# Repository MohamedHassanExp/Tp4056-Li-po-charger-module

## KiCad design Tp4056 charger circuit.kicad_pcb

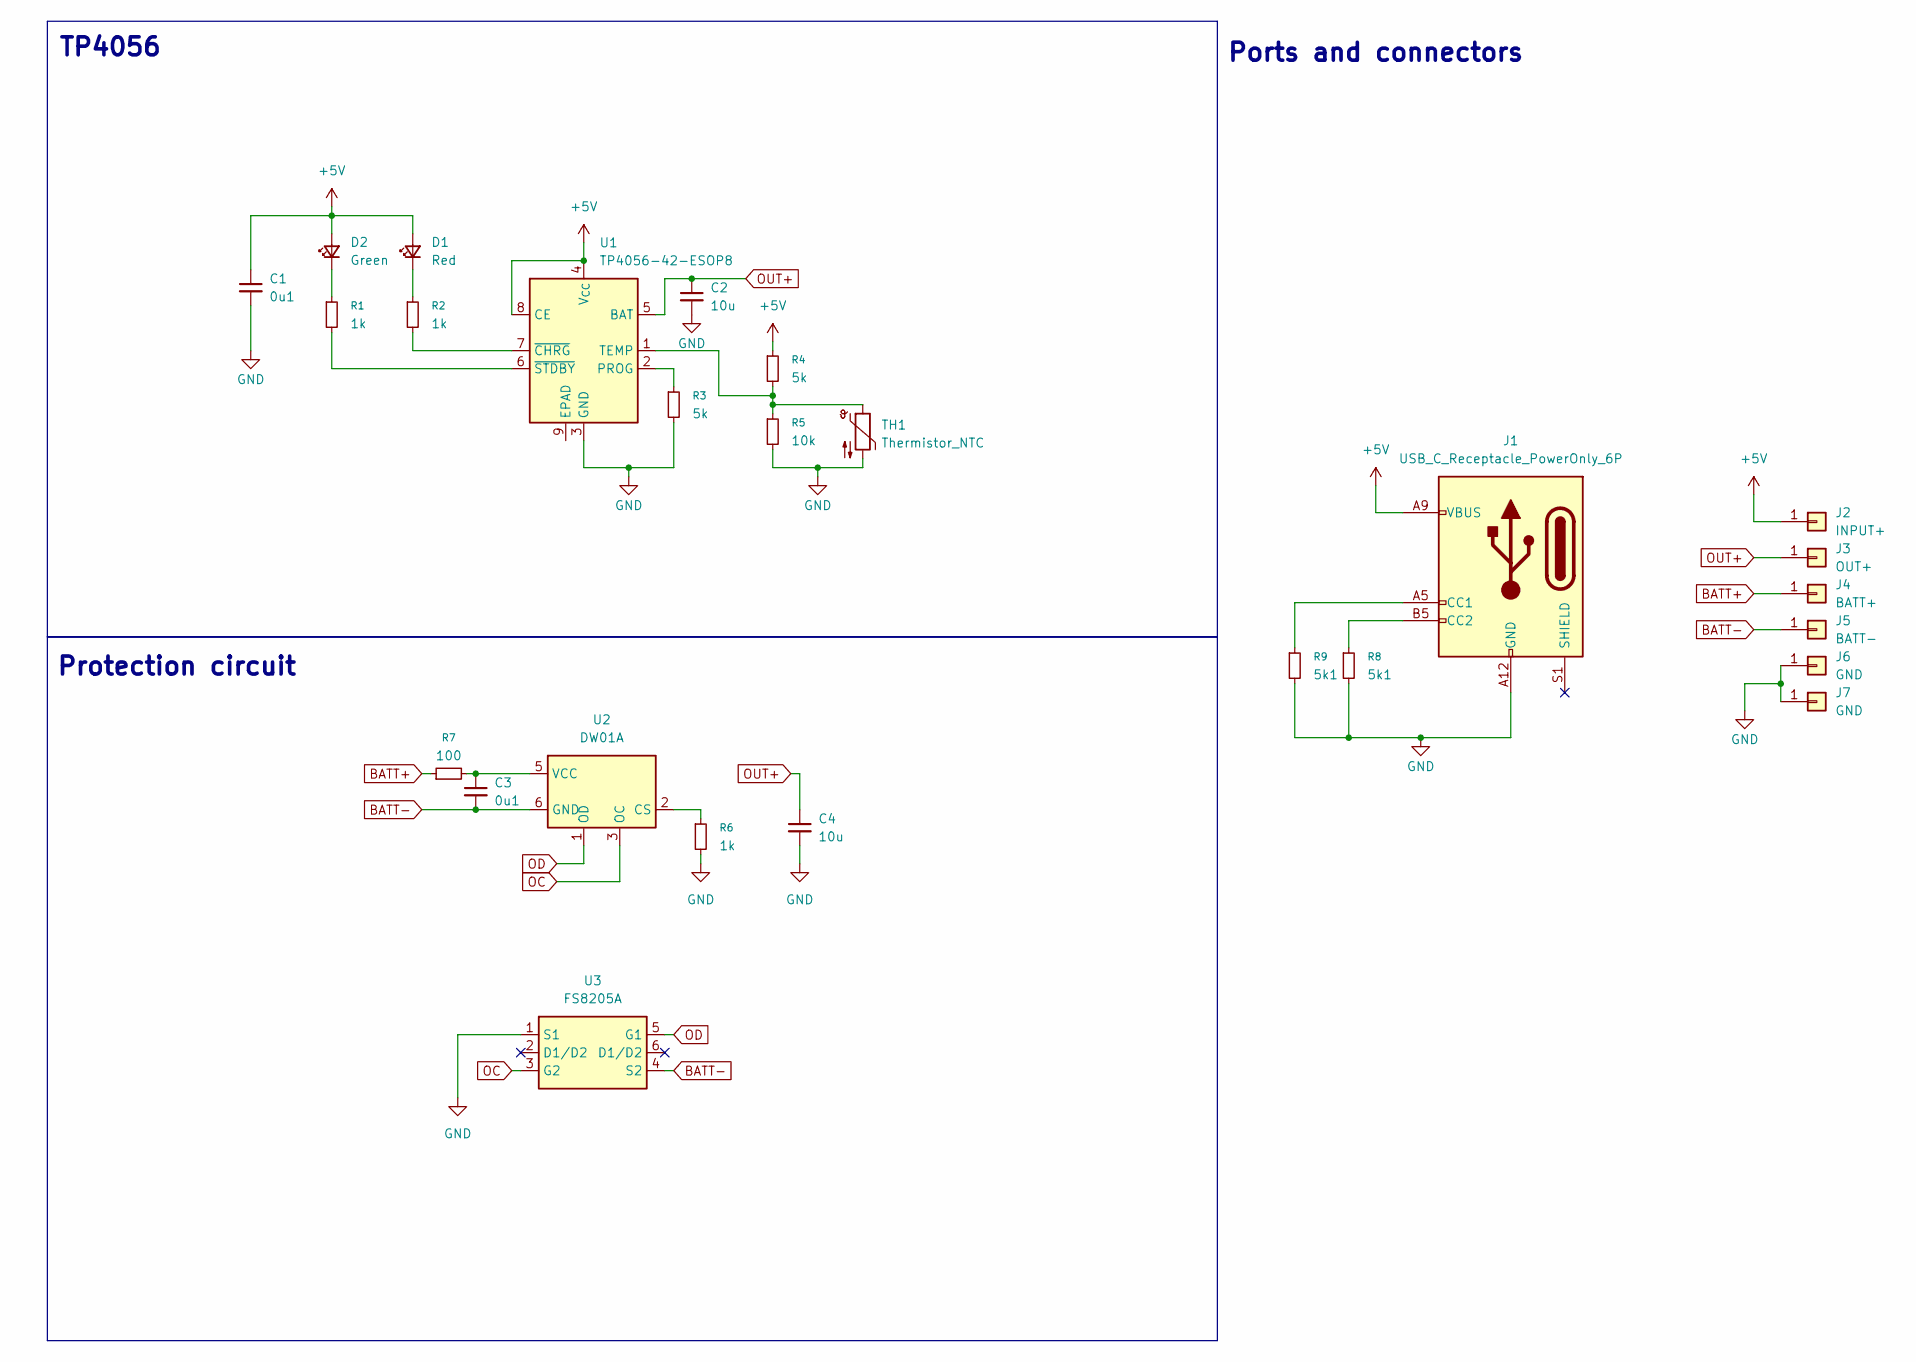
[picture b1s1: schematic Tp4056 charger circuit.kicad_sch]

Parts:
C1, C3: 0u1; C_0603_1608Metric
C2, C4: 10u; C_0603_1608Metric
D1: Red; LED_0603_1608Metric
D2: Green; LED_0603_1608Metric
J1: USB_C_Receptacle_PowerOnly_6P; USB_C_Receptacle_GCT_USB4125-xx-x_6P_TopMnt_Horizontal
J2: INPUT+; TestPoint_THTPad_3.0x3.0mm_Drill1.5mm
J3: OUT+; TestPoint_THTPad_3.0x3.0mm_Drill1.5mm
J4: BATT+; TestPoint_THTPad_3.0x3.0mm_Drill1.5mm
J5: BATT-; TestPoint_THTPad_3.0x3.0mm_Drill1.5mm
J6, J7: GND; TestPoint_THTPad_3.0x3.0mm_Drill1.5mm
R1, R2, R6: 1k; R_0603_1608Metric
R3, R4: 5k; R_0603_1608Metric
R5: 10k; R_0603_1608Metric
R7: 100; R_0603_1608Metric
R8, R9: 5k1; R_0603_1608Metric
TH1: Thermistor_NTC; TestPoint_2Pads_Pitch2.54mm_Drill0.8mm
U1: TP4056-42-ESOP8; SOIC-8-1EP_3.9x4.9mm_P1.27mm_EP2.41x3.3mm_ThermalVias
U2: DW01A; SOT-23-6
U3: FS8205A; SOT-23-6

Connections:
+5V: C1.1, D1.2 (A), D2.2 (A), J1.A9 (VBUS), J1.B9 (VBUS), J2.1, R4.1, U1.4 (V_{CC}), U1.8 (CE)
BATT+: J4.1, R7.1
BATT-: C3.2, J5.1, U2.6 (GND), U3.4 (S2)
GND: C1.2, C2.2, C4.2, J1.A12 (GND), J1.B12 (GND), J6.1, J7.1, R3.2, R5.2, R6.2, R8.2, R9.2, TH1.2, U1.3 (GND), U3.1 (S1)
unnamed: D1.1 (K), R2.1
unnamed: D2.1 (K), R1.1
unnamed: J1.A5 (CC1), R9.1
unnamed: J1.B5 (CC2), R8.1
unnamed: R3.1, U1.2 (PROG)
unnamed: R4.2, R5.1, TH1.1, U1.1 (TEMP)
unnamed: R2.2, U1.7 (~CHRG)
unnamed: R1.2, U1.6 (~STDBY)
unnamed: R6.1, U2.2 (CS)
unnamed: C3.1, R7.2, U2.5 (VCC)
OC: U2.3 (OC), U3.3 (G2)
OD: U2.1 (OD), U3.5 (G1)
OUT+: C2.1, C4.1, J3.1, U1.5 (BAT)

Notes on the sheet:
TP4056
Protection circuit
Ports and connectors

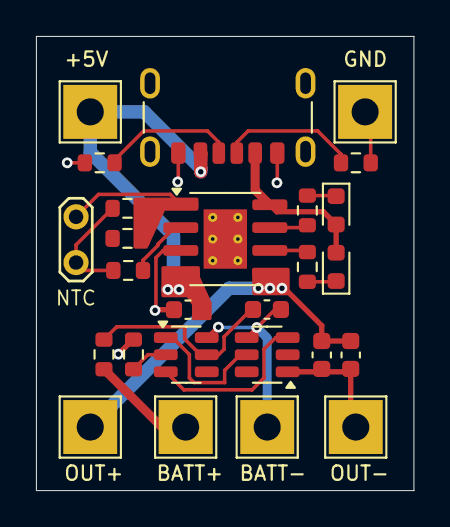
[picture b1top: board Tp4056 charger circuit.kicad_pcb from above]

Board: 2 copper layers, 21.0 x 25.2 mm, 26 parts (0 on the bottom side), 17 nets.

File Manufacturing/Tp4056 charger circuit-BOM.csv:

"Id";"Designator";"Footprint";"Quantity";"Designation";"Supplier and ref";
1;"TH1";"TestPoint_2Pads_Pitch2.54mm_Drill0.8mm";1;"Thermistor_NTC";;;
2;"J6,J7";"TestPoint_THTPad_3.0x3.0mm_Drill1.5mm";2;"GND";;;
3;"R3,R4";"R_0603_1608Metric";2;"5k";;;
4;"J2";"TestPoint_THTPad_3.0x3.0mm_Drill1.5mm";1;"INPUT+";;;
5;"R2,R1,R6";"R_0603_1608Metric";3;"1k";;;
6;"C2,C4";"C_0603_1608Metric";2;"10u";;;
7;"U3";"SOT-23-6";1;"FS8205A";;;
8;"R7";"R_0603_1608Metric";1;"100";;;
9;"J3";"TestPoint_THTPad_3.0x3.0mm_Drill1.5mm";1;"OUT+";;;
10;"J1";"USB_C_Receptacle_GCT_USB4125-xx-x_6P_TopMnt_Horizontal";1;"USB_C_Receptacle_PowerOnly_6P";;;
11;"J4";"TestPoint_THTPad_3.0x3.0mm_Drill1.5mm";1;"BATT+";;;
12;"D1";"LED_0603_1608Metric";1;"Red";;;
13;"C1,C3";"C_0603_1608Metric";2;"0u1";;;
14;"R9,R8";"R_0603_1608Metric";2;"5k1";;;
15;"U1";"SOIC-8-1EP_3.9x4.9mm_P1.27mm_EP2.41x3.3mm_ThermalVias";1;"TP4056-42-ESOP8";;;
16;"R5";"R_0603_1608Metric";1;"10k";;;
17;"D2";"LED_0603_1608Metric";1;"Green";;;
18;"U2";"SOT-23-6";1;"DW01A";;;
19;"J5";"TestPoint_THTPad_3.0x3.0mm_Drill1.5mm";1;"BATT-";;;
